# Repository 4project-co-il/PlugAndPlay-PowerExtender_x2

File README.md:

# PlugAndPlay: Power Extender x2
This is the repository with the files for PlugAndPlay power externder board.

The board has 3x PnP power module ports and allows connection of 3x PnP power modules.
All the ports are connected in parallel. One port will be used as an input and 2x ports as extended outputs.

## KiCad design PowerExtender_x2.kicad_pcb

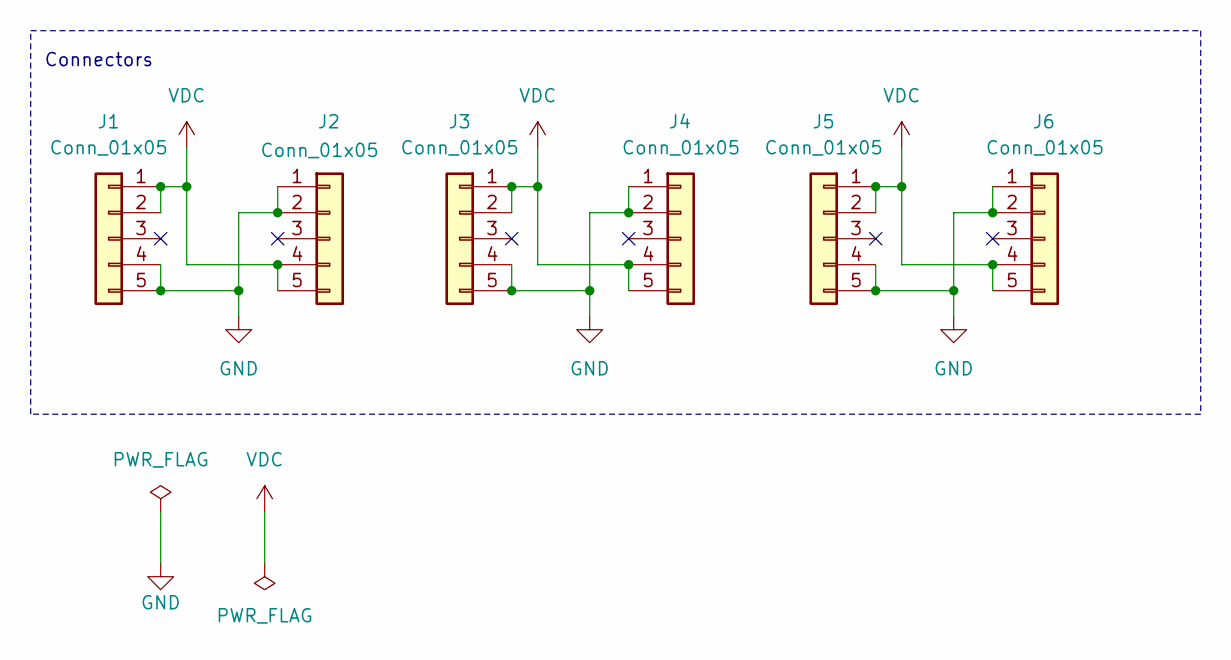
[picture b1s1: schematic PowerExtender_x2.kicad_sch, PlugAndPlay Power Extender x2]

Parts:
J1, J3, J5: Conn_01x05; PinSocket_1x05_P2.54mm_Vertical_SMD_Pin1Right; MPN RealRun
J2, J4, J6: Conn_01x05; PinSocket_1x05_P2.54mm_Vertical_SMD_Pin1Left; MPN RealRun

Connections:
GND: J1.4, J1.5, J2.1, J2.2, J3.4, J3.5, J4.1, J4.2, J5.4, J5.5, J6.1, J6.2
VDC: J1.1, J1.2, J2.4, J2.5, J3.1, J3.2, J4.4, J4.5, J5.1, J5.2, J6.4, J6.5

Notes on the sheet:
Connectors

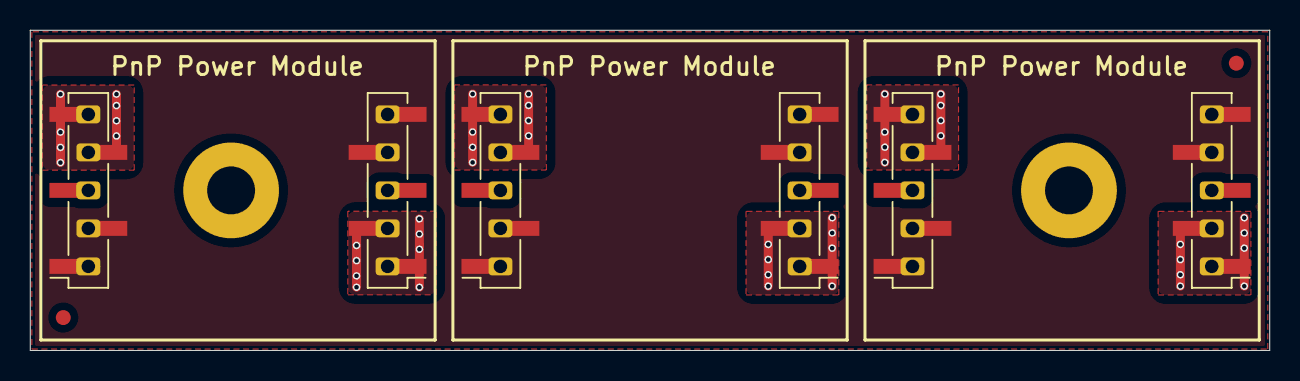
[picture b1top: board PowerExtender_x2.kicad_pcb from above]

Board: 2 copper layers, 82.8 x 21.4 mm, 6 parts (0 on the bottom side), 2 nets.
